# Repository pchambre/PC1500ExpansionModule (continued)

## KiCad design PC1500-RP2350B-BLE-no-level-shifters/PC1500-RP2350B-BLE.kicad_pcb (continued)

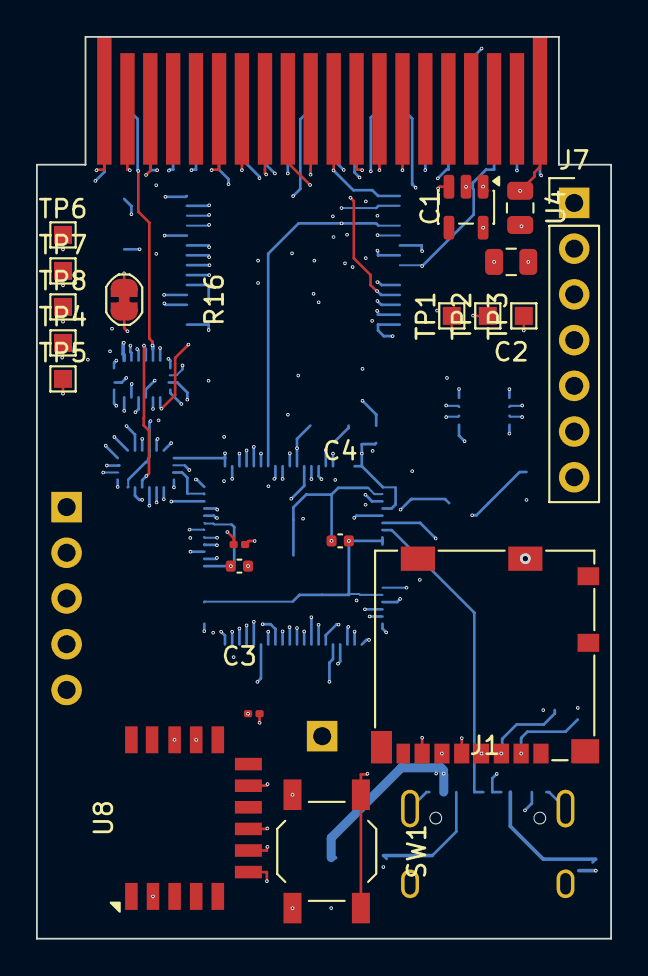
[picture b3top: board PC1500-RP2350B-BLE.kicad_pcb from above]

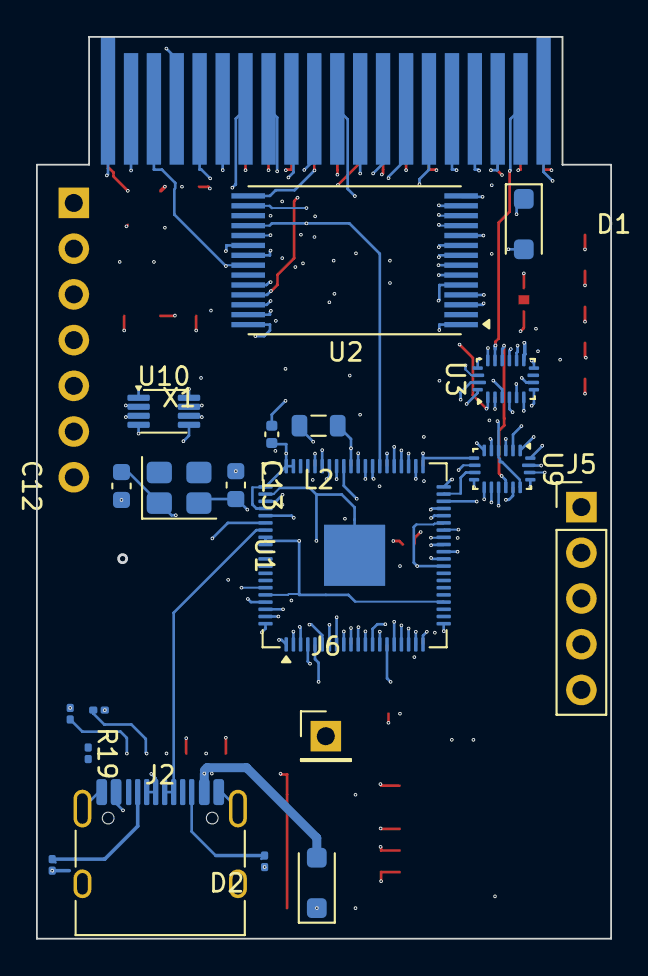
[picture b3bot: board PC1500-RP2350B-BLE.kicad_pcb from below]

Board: 8 copper layers, 31.9 x 50.1 mm, 41 parts (20 on the bottom side), 77 nets.

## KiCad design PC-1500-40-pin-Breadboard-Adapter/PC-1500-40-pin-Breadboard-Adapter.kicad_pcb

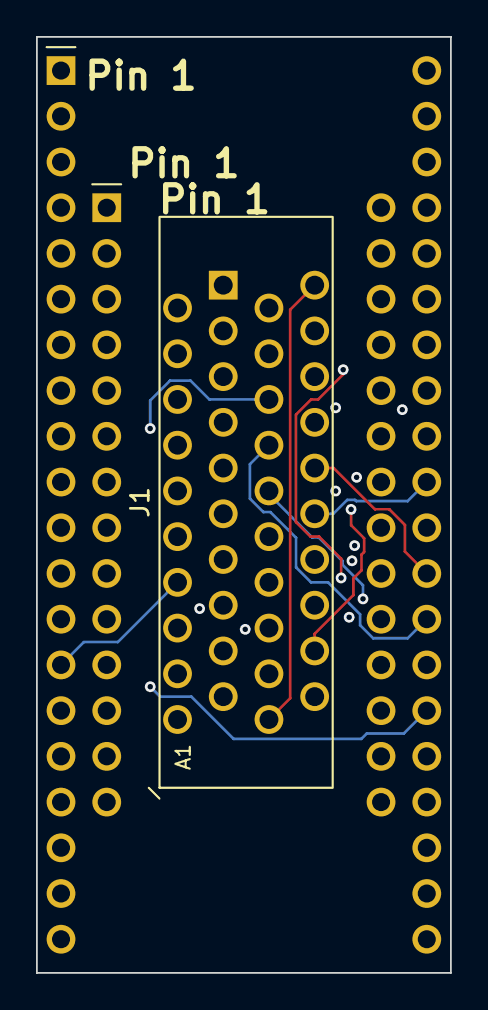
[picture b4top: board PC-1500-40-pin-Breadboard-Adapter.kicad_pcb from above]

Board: 4 copper layers, 23.0 x 52.0 mm, 3 parts (0 on the bottom side), 39 nets.

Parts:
J1: RBB20DHHN; Sullins_RBB20DHHN_2x20_P1.27mm_Staggered
J2: DIP-40 0.8in (breadboard); DIP-40_W20.32mm_Holes
J3: DIP-28 0.6in (EPROM socket); DIP-28_W15.24mm_Holes

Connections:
/AD0: J1.37, J2.37
/AD1: J1.36, J2.36
/AD2: J1.35, J2.35
/AD3: J1.34, J2.34
/AD4: J1.33, J2.33
/AD5: J1.32, J2.32
/AD6: J1.31, J2.31
/AD7: J1.30, J2.30
/AD8: J1.29, J2.29
/AD9: J1.28, J2.28
/AD10: J1.27, J2.27
/AD11: J1.26, J2.26
/AD12: J1.25, J2.25
/AD13: J1.24, J2.24
/AD14: J1.23, J2.23
/AD15: J1.22, J2.22
/CART_PIN5: J1.5, J2.5
/D0: J1.14, J2.14
/D1: J1.13, J2.13
/D2: J1.12, J2.12
/D3: J1.11, J2.11
/D4: J1.10, J2.10
/D5: J1.9, J2.9
/D6: J1.8, J2.8
/D7: J1.7, J2.7
/DME0: J1.6, J2.6
/GND: J1.21, J1.40, J2.21, J2.40
/INHIBIT: J1.15, J2.15
/OD: J1.38, J2.38
/PU: J1.2, J2.2
/PV: J1.3, J2.3
/RW: J1.39, J2.39
/S1: J1.16, J2.16
/S2: J1.17, J2.17
/S3: J1.18, J2.18
/VCC: J1.1, J2.1
/VGG: J1.20, J2.20
/Y0: J1.4, J2.4
/Y2: J1.19, J2.19

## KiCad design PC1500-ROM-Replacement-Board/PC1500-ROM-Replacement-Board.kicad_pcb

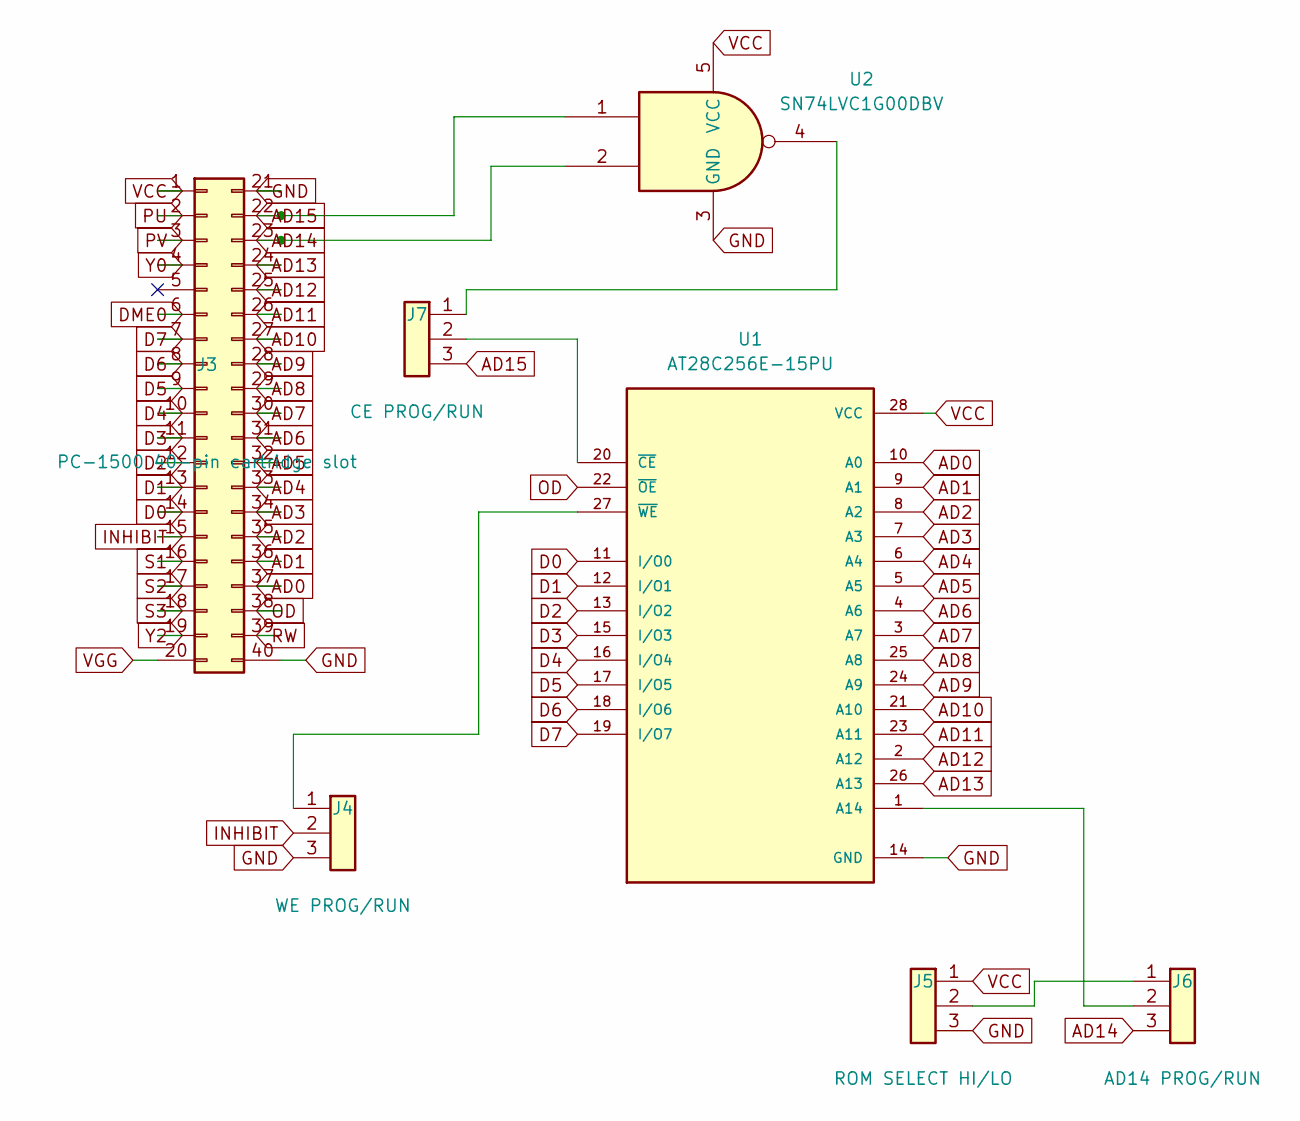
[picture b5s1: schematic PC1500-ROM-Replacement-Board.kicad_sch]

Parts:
J3: PC-1500 40-pin cartridge slot; SHARP-PC-CARTRIDGE
J4: WE PROG/RUN; PinHeader_1x03_P2.54mm_Vertical
J5: ROM SELECT HI/LO; PinHeader_1x03_P2.54mm_Vertical
J6: AD14 PROG/RUN; PinHeader_1x03_P2.54mm_Vertical
J7: CE PROG/RUN; PinHeader_1x03_P2.54mm_Vertical
U1: AT28C256E-15PU; SOIC-28W_7.5x17.9mm_P1.27mm; PARTREV B
U2: SN74LVC1G00DBV; SOT-23-5

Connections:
AD0: J3.37, U1.10 (A0)
AD1: J3.36, U1.9 (A1)
AD2: J3.35, U1.8 (A2)
AD3: J3.34, U1.7 (A3)
AD4: J3.33, U1.6 (A4)
AD5: J3.32, U1.5 (A5)
AD6: J3.31, U1.4 (A6)
AD7: J3.30, U1.3 (A7)
AD8: J3.29, U1.25 (A8)
AD9: J3.28, U1.24 (A9)
AD10: J3.27, U1.21 (A10)
AD11: J3.26, U1.23 (A11)
AD12: J3.25, U1.2 (A12)
AD13: J3.24, U1.26 (A13)
AD14: J3.23, J6.3, U2.2
AD15: J3.22, J7.3, U2.1
D0: J3.14, U1.11 (I/O0)
D1: J3.13, U1.12 (I/O1)
D2: J3.12, U1.13 (I/O2)
D3: J3.11, U1.15 (I/O3)
D4: J3.10, U1.16 (I/O4)
D5: J3.9, U1.17 (I/O5)
D6: J3.8, U1.18 (I/O6)
D7: J3.7, U1.19 (I/O7)
DME0: J3.6
GND: J3.21, J3.40, J4.3, J5.3, U1.14 (GND), U2.3 (GND)
INHIBIT: J3.15, J4.2
unnamed: J4.1, U1.27 (~WE)
unnamed: J5.2, J6.1
unnamed: J6.2, U1.1 (A14)
unnamed: J7.1, U2.4
unnamed: J7.2, U1.20 (~CE)
OD: J3.38, U1.22 (~OE)
PU: J3.2
PV: J3.3
RW: J3.39
S1: J3.16
S2: J3.17
S3: J3.18
VCC: J3.1, J5.1, U1.28 (VCC), U2.5 (VCC)
VGG: J3.20
Y0: J3.4
Y2: J3.19

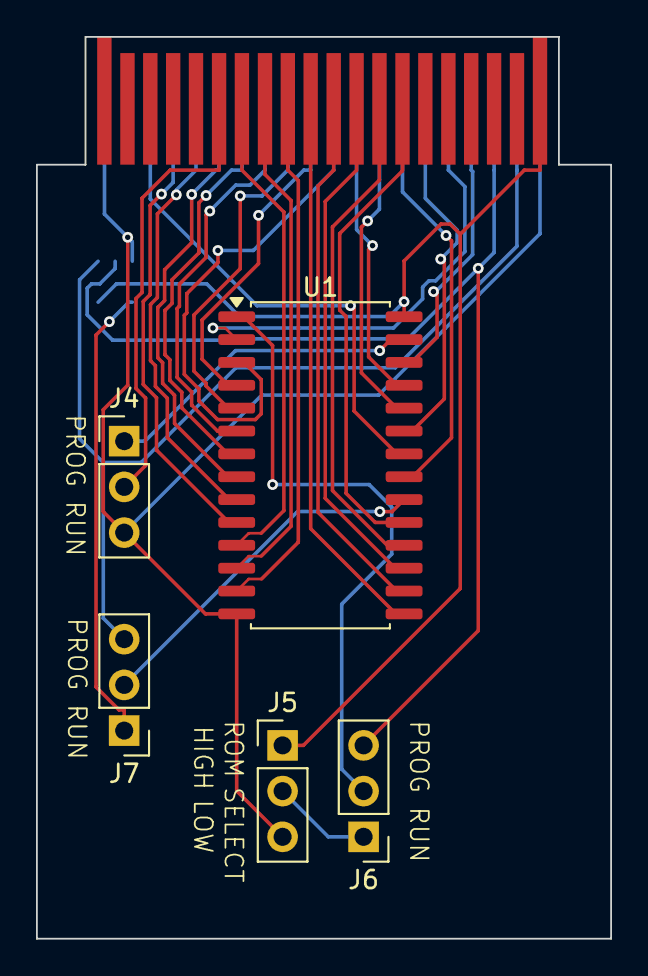
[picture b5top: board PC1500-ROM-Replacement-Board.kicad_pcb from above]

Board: 2 copper layers, 31.9 x 50.1 mm, 7 parts (1 on the bottom side), 33 nets.

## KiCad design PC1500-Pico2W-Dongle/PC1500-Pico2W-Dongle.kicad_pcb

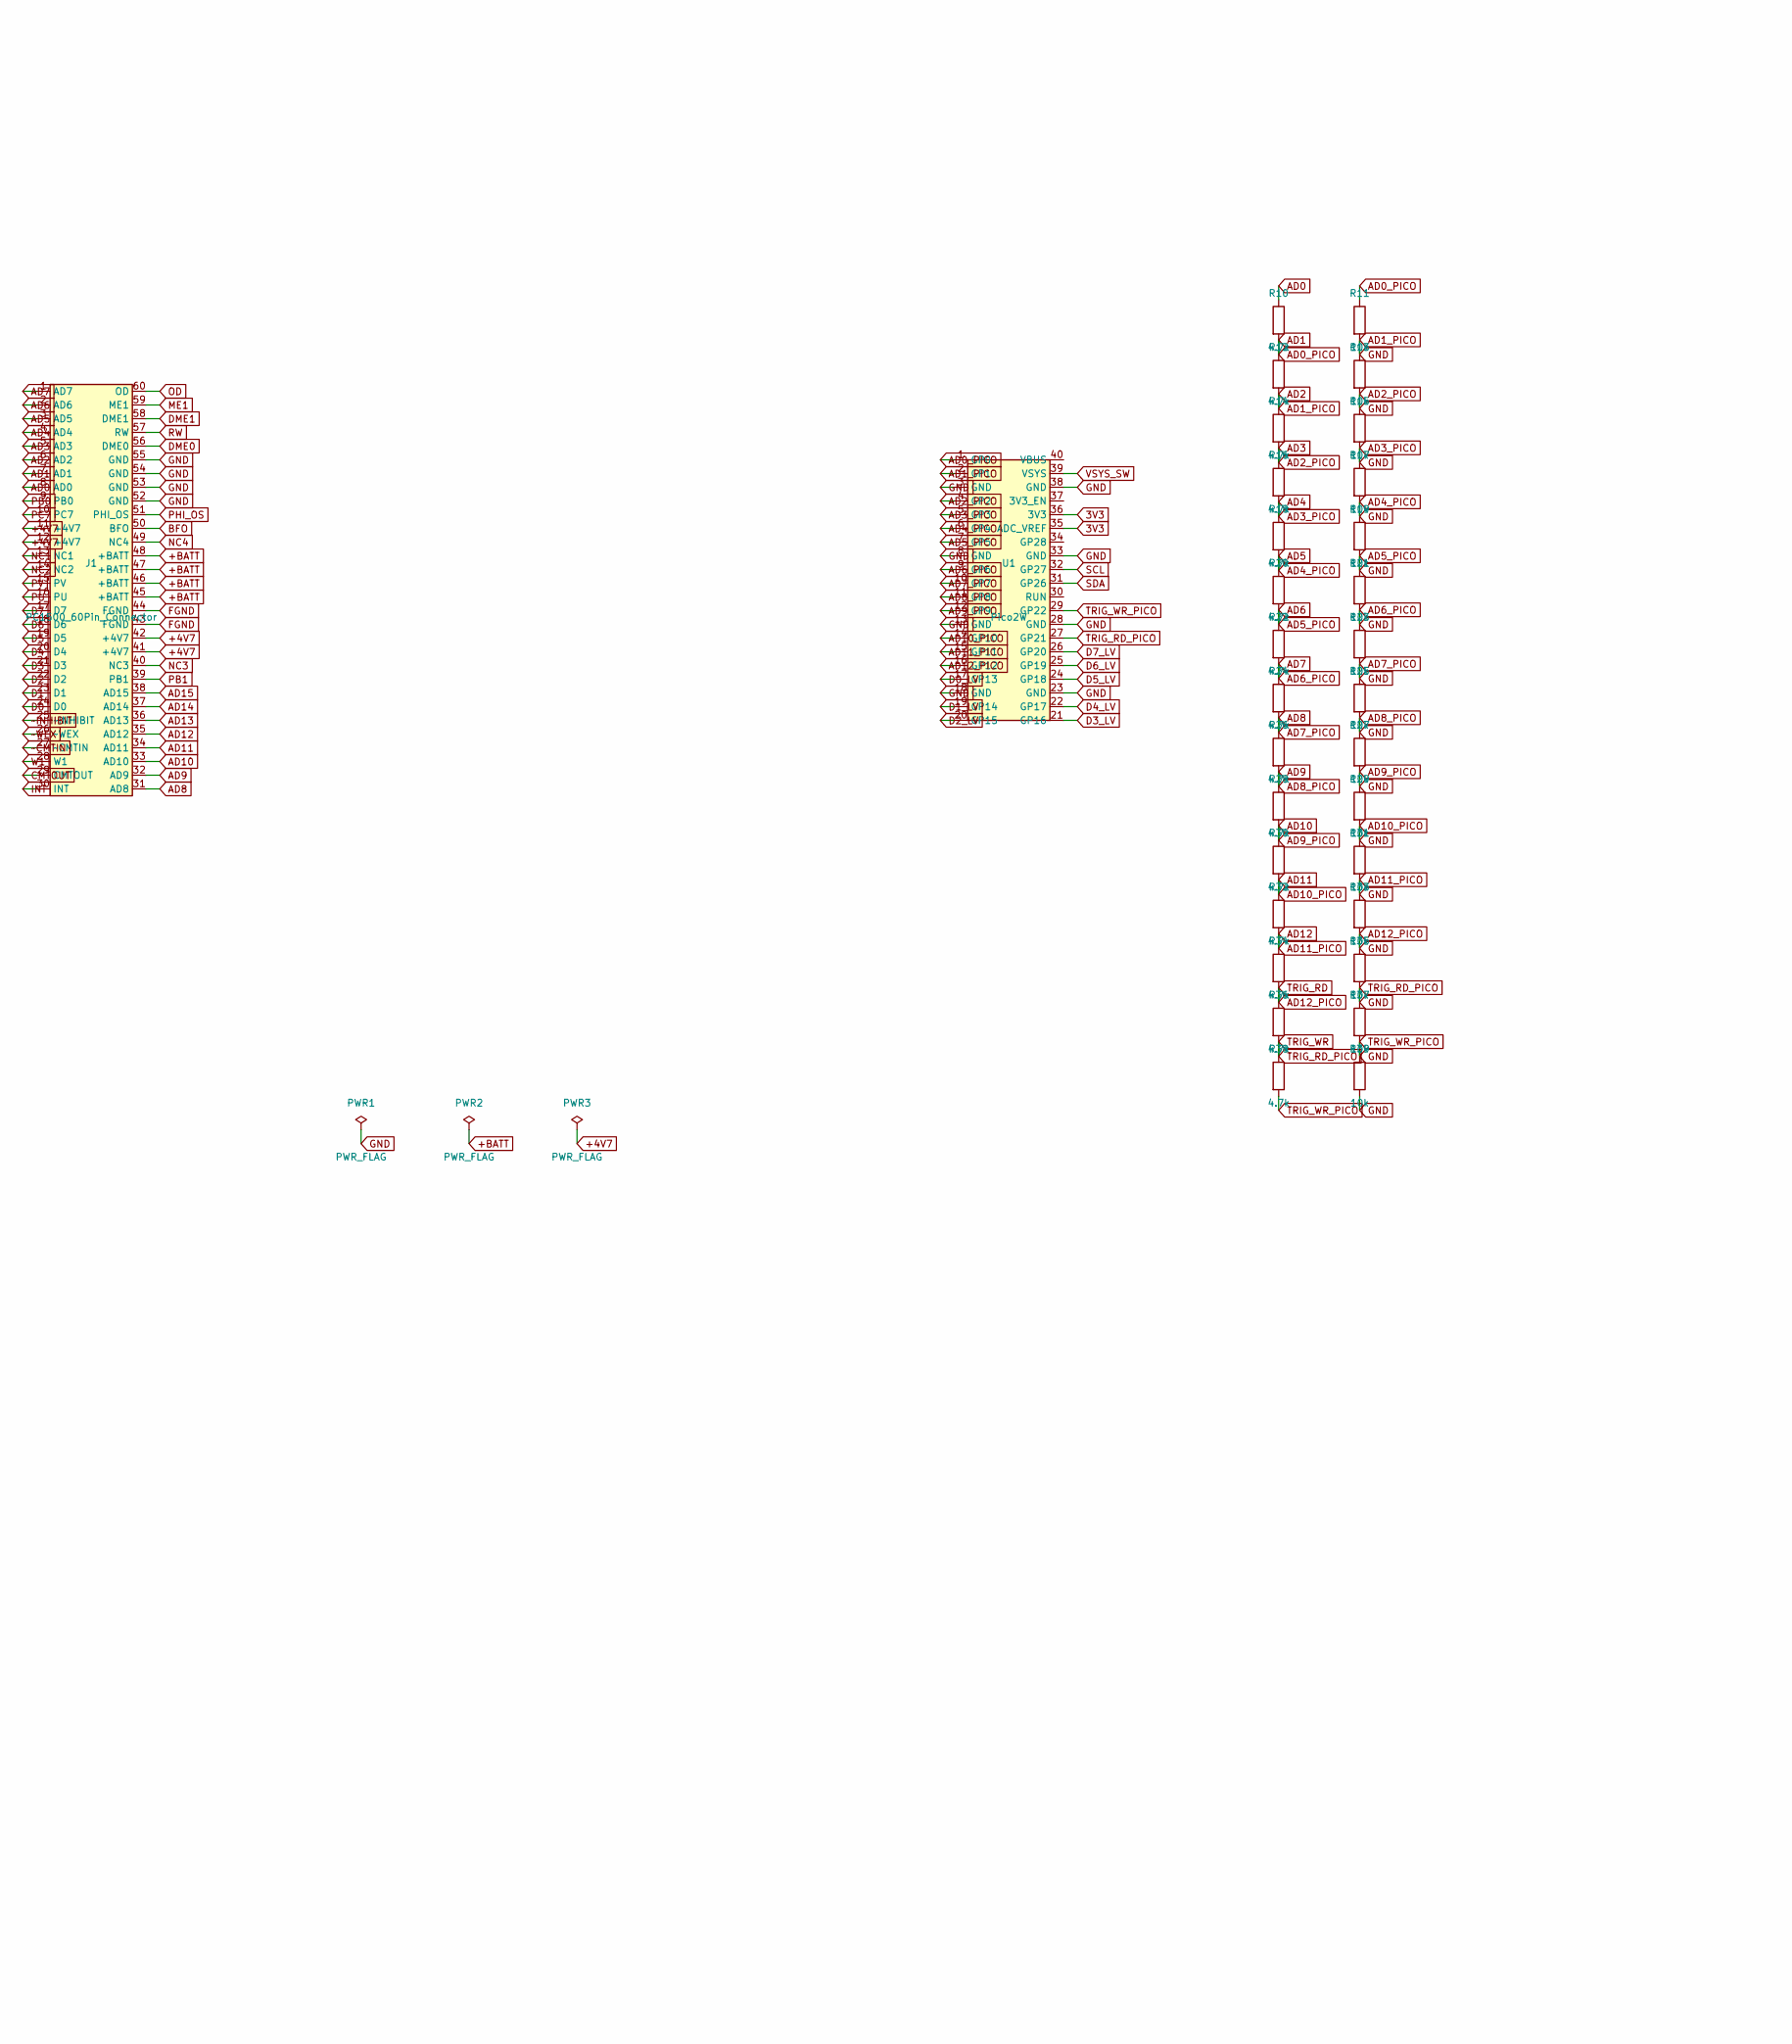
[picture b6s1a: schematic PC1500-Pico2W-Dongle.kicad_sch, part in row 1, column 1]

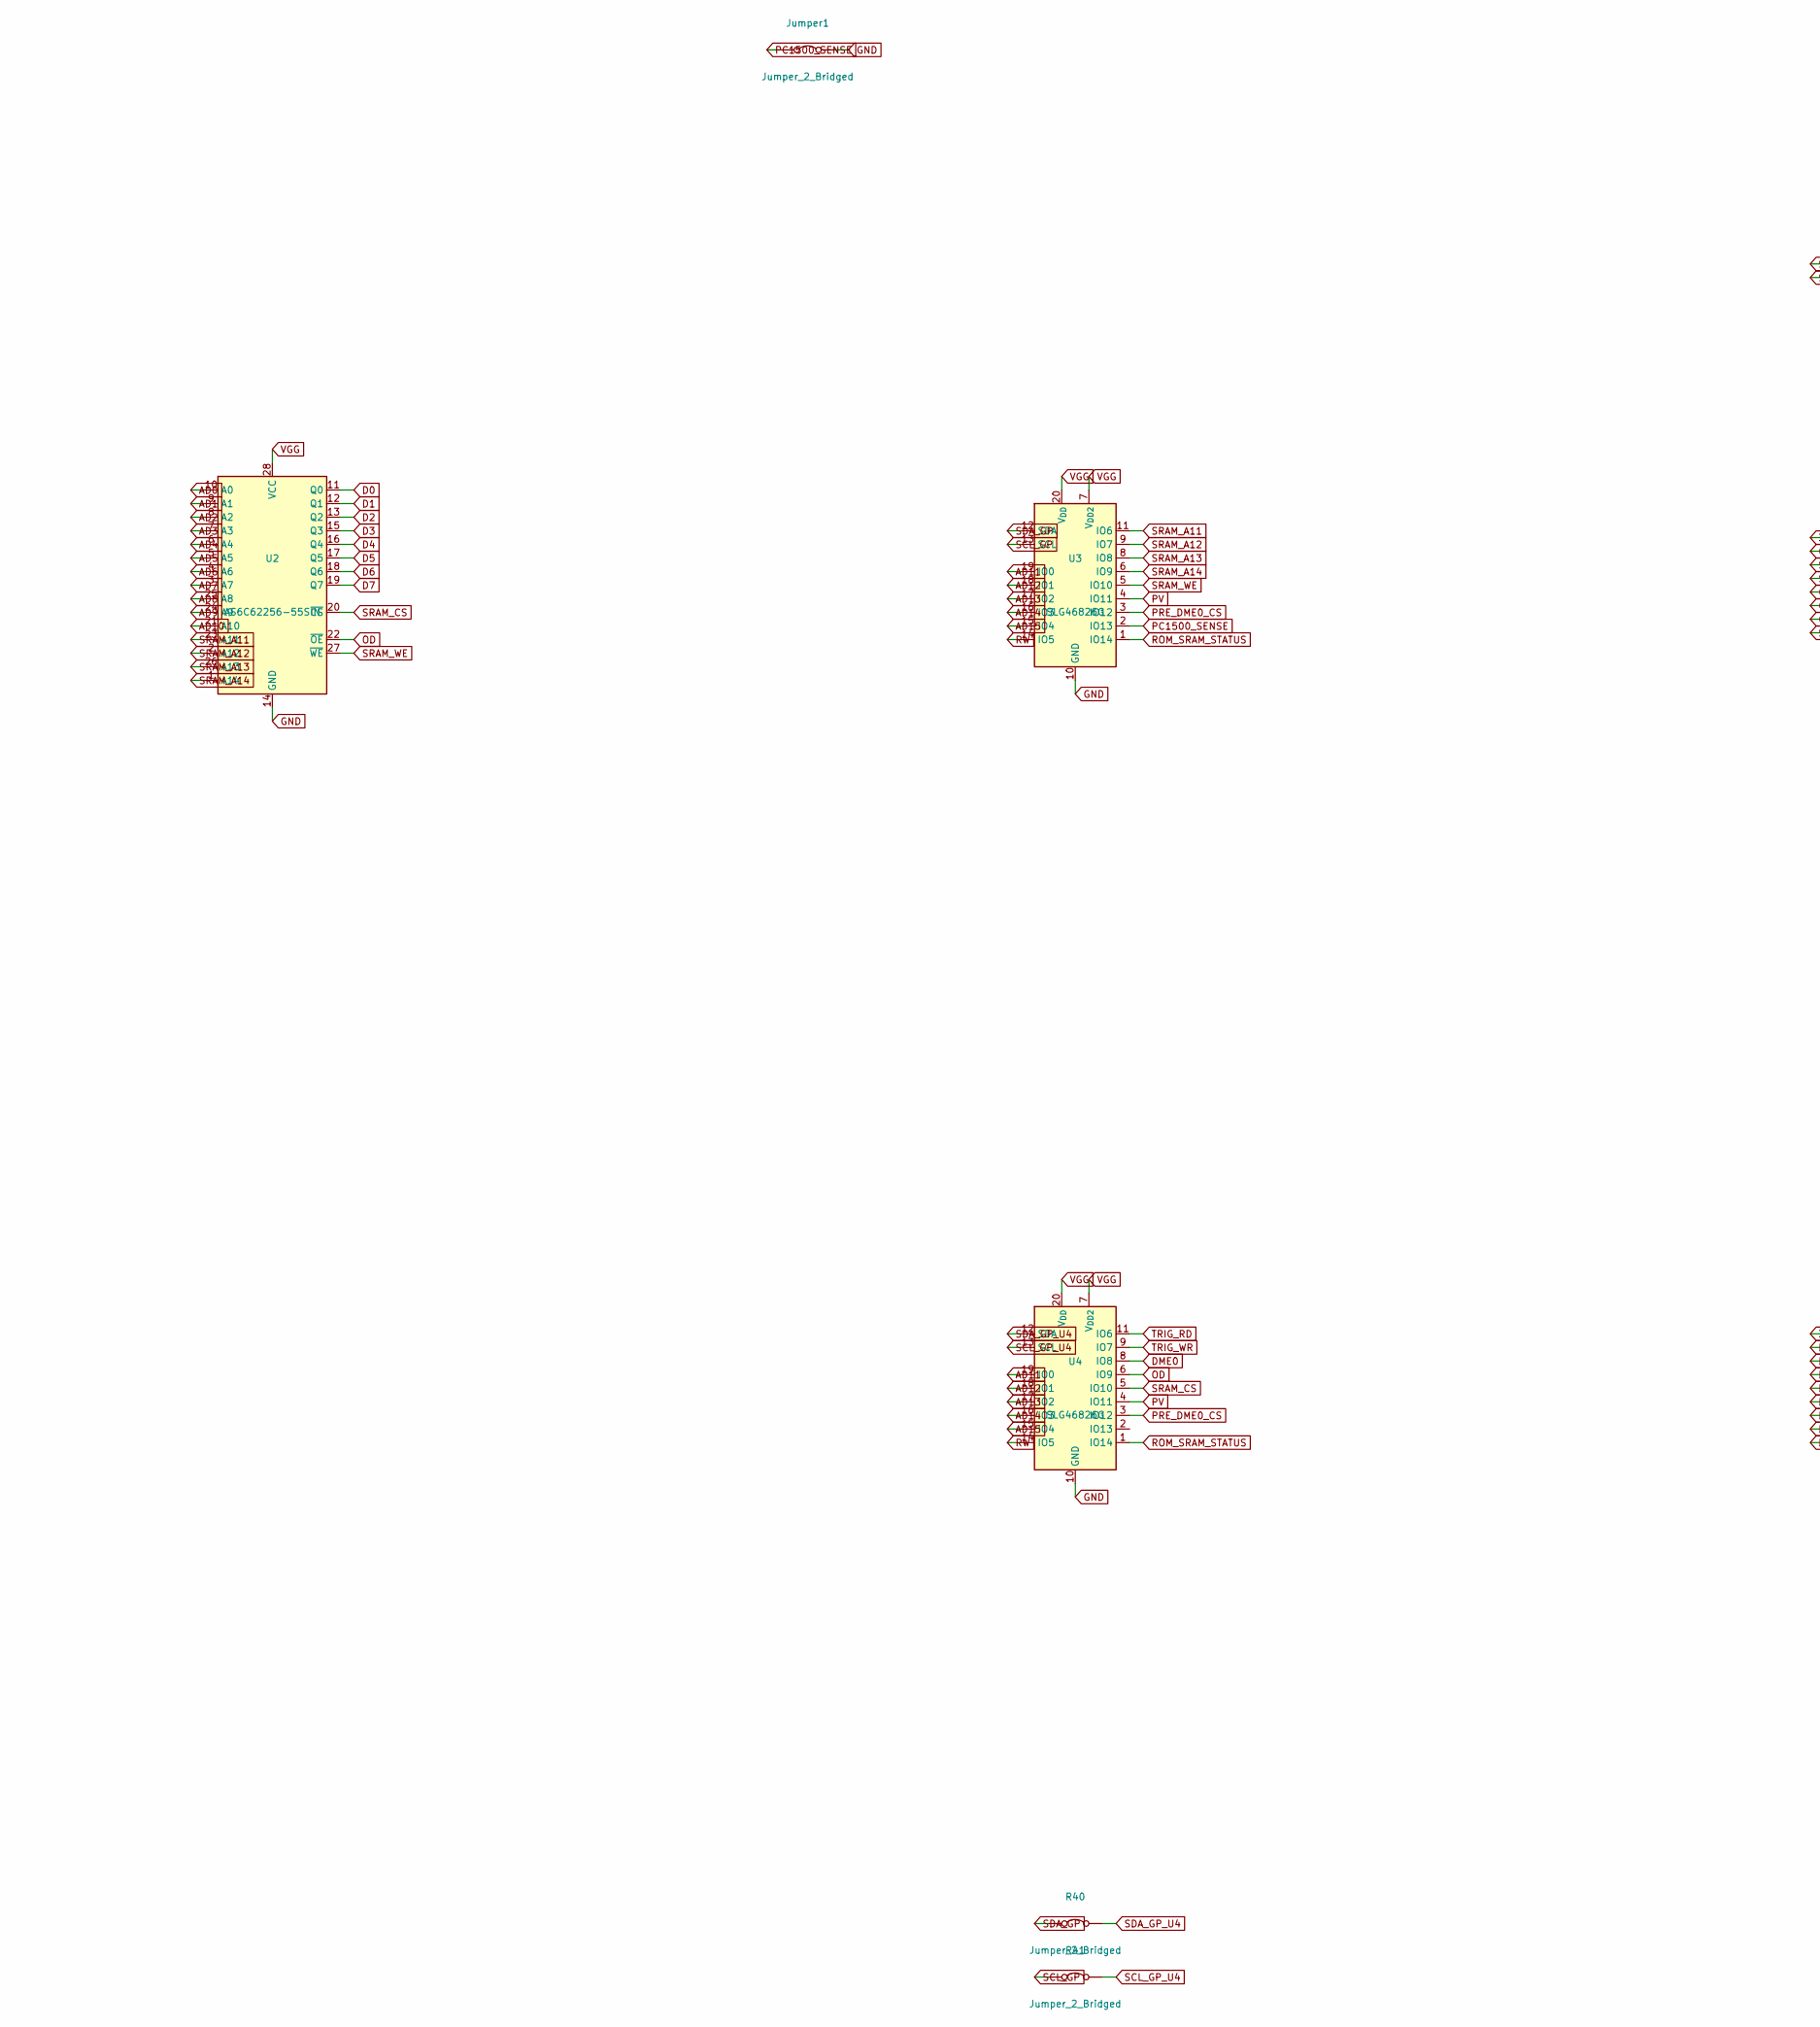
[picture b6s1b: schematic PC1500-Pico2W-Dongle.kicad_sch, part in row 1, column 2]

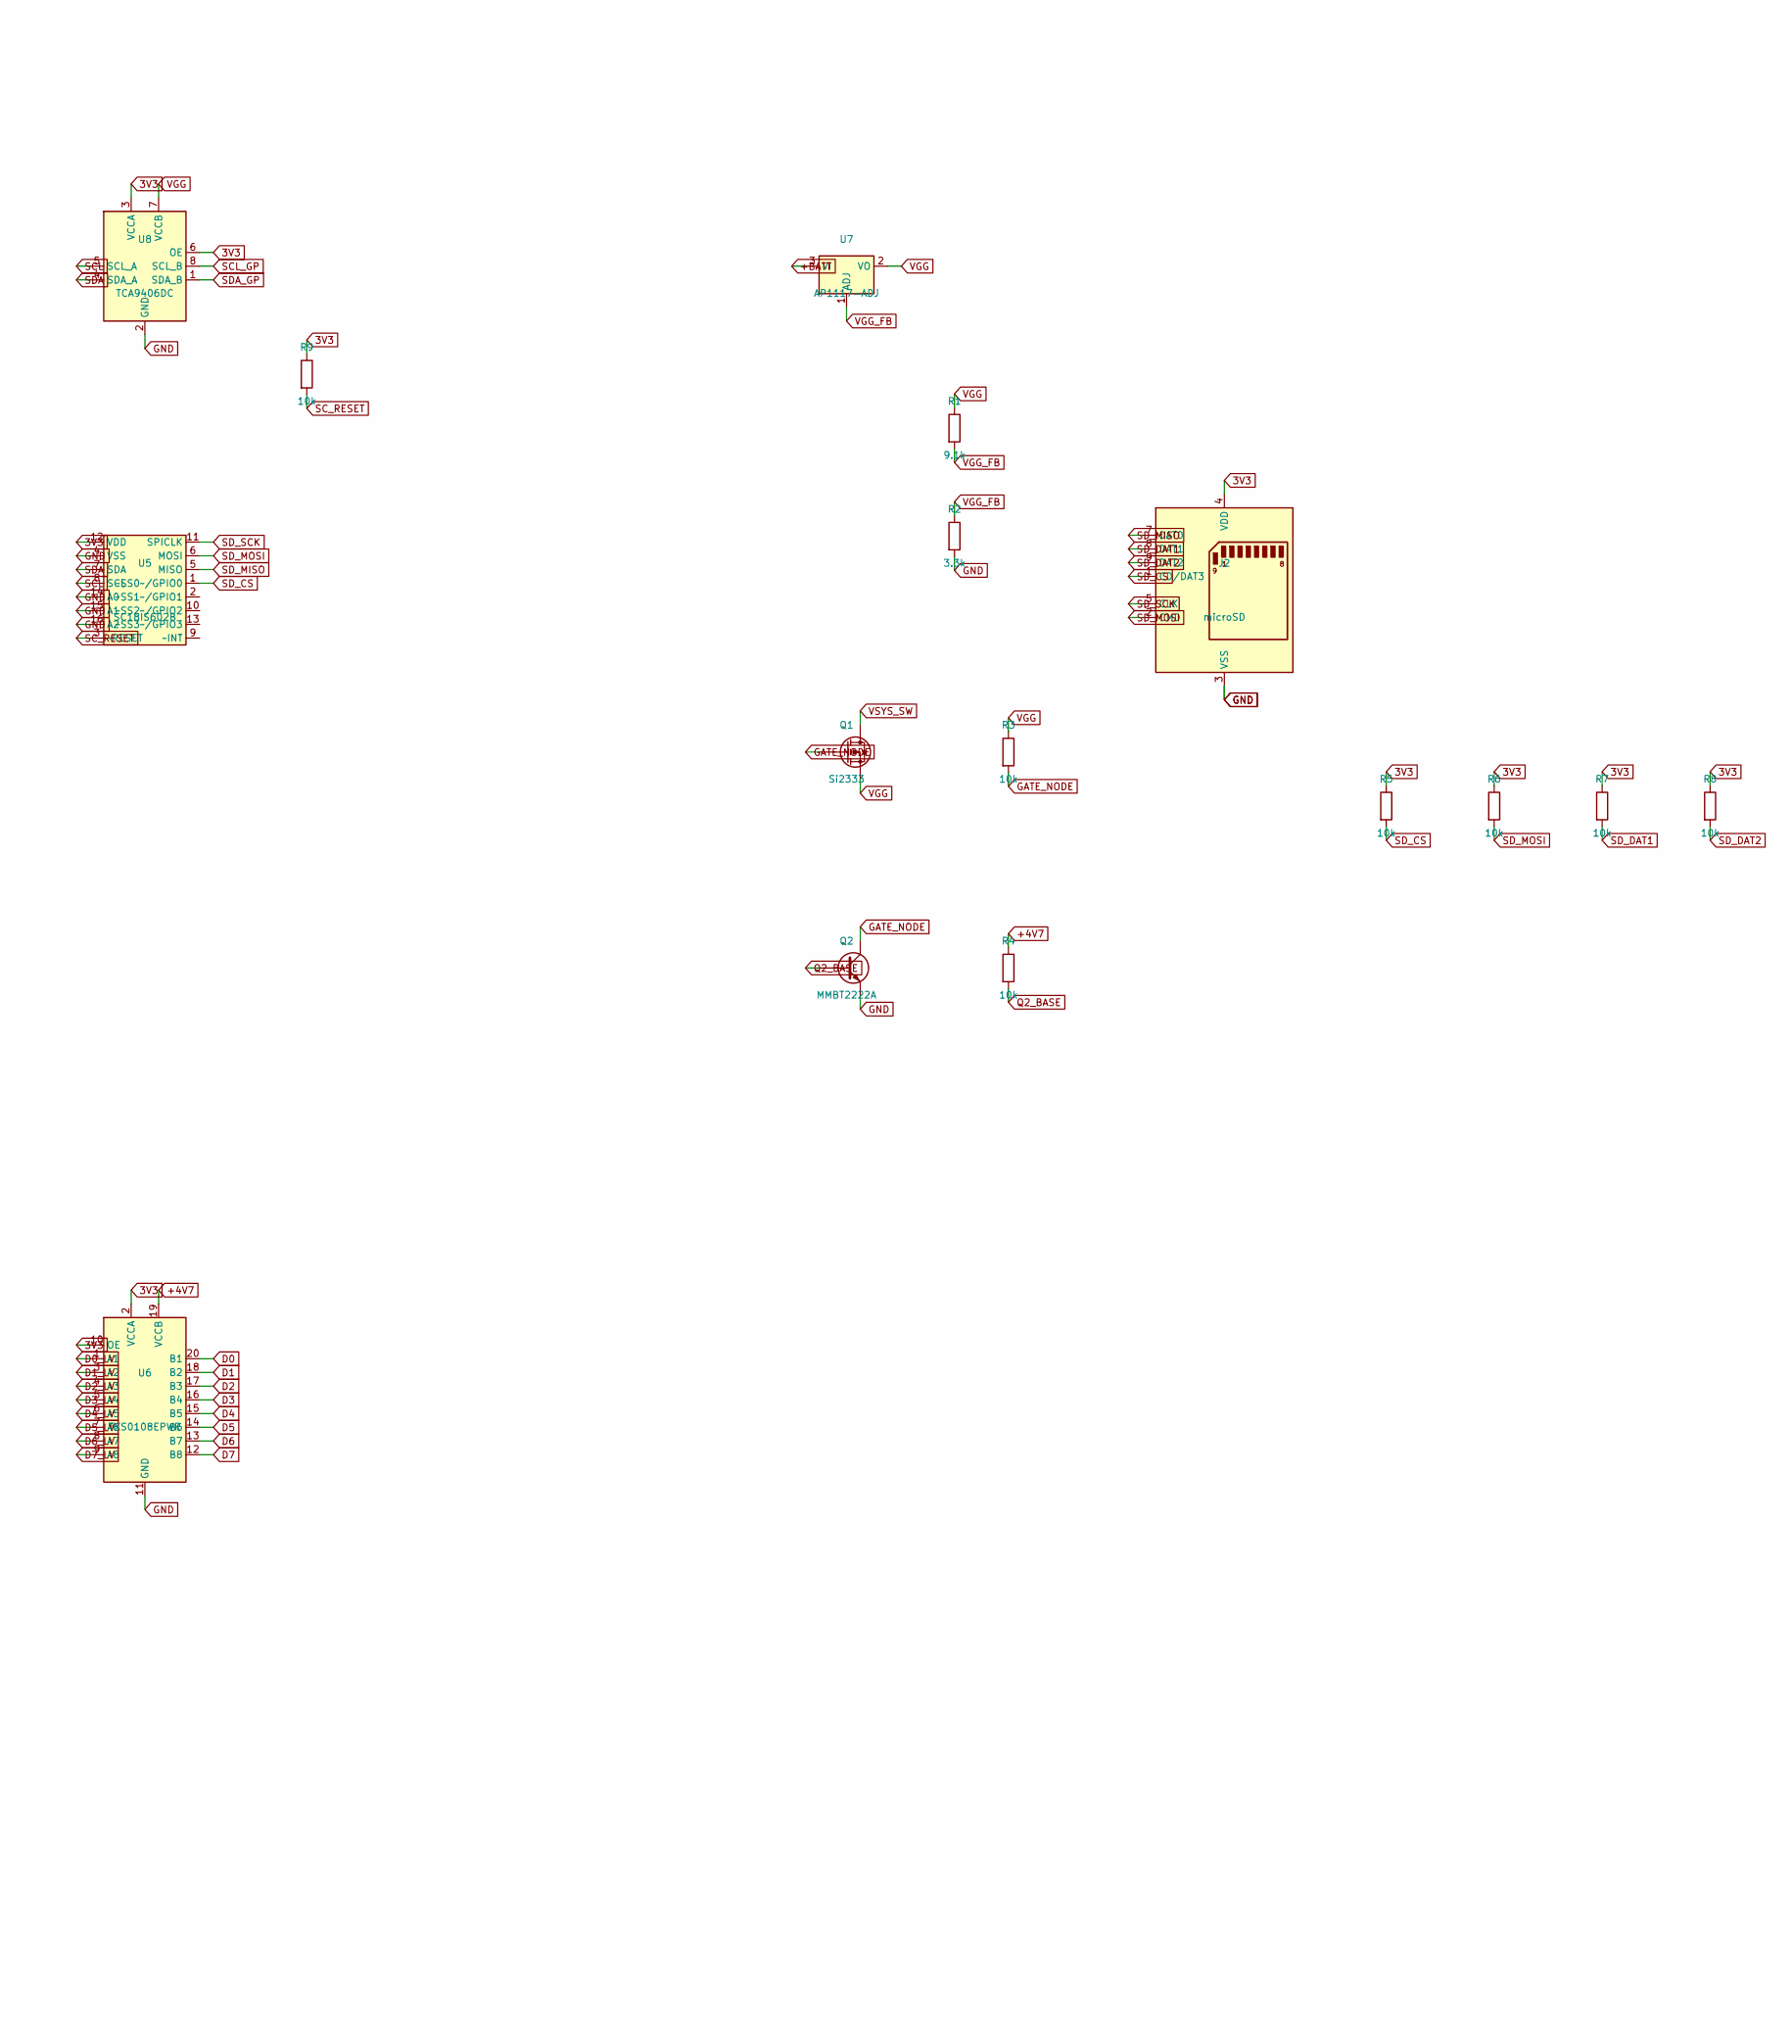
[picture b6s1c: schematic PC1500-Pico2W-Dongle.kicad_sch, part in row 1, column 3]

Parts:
J1: PC1500_60Pin_Connector; HIF6A-60PA-1.27DS
J2: microSD; microSD_HC_Molex_104031-0811
Jumper1: Jumper_2_Bridged; SolderJumper-2_P1.3mm_Bridged_RoundedPad1.0x1.5mm
PWR1, PWR2, PWR3: PWR_FLAG
Q1: Si2333; SOT-23
Q2: MMBT2222A; SOT-23
R1: 9.1k; R_0201_0603Metric
R2: 3.3k; R_0201_0603Metric
R3, R4, R5, R6, R7, R8, R9, R11, R13, R15, R17, R19, R21, R23, R25, R27, R29, R31, R33, R35, R37, R39: 10k; R_0201_0603Metric
R10, R12, R14, R16, R18, R20, R22, R24, R26, R28, R30, R32, R34, R36, R38: 4.7k; R_0201_0603Metric
R40, R41: Jumper_2_Bridged; SolderJumper-2_P1.3mm_Bridged_RoundedPad1.0x1.5mm
U1: Pico2W; Pico2W-Socket
U2: AS6C62256-55SIN; SOP-28_8.4x18.16mm_P1.27mm
U3, U4: SLG46826G; TSSOP-20_4.4x6.5mm_P0.65mm
U5: SC18IS602B; TSSOP-16_4.4x5mm_P0.65mm
U6: TXS0108EPWR; TSSOP-20_4.4x6.5mm_P0.65mm
U7: AP1117-ADJ; SOT-223-3_TabPin2
U8: TCA9406DC; VSSOP-8_3x3mm_P0.65mm

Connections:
3V3: J2.4 (VDD), R5.1, R6.1, R7.1, R8.1, R9.1, U1.35 (ADC_VREF), U1.36 (3V3), U5.12 (VDD), U6.2 (VCCA), U6.10 (OE), U8.3 (VCCA), U8.6 (OE)
+4V7: J1.11 (+4V7), J1.12 (+4V7), J1.41 (+4V7), J1.42 (+4V7), PWR3.1, R4.1, U6.19 (VCCB)
+BATT: J1.45 (+BATT), J1.46 (+BATT), J1.47 (+BATT), J1.48 (+BATT), PWR2.1, U7.3 (VI)
AD0: J1.8 (AD0), R10.1, U2.10 (A0)
AD0_PICO: R10.2, R11.1, U1.1 (GP0)
AD1: J1.7 (AD1), R12.1, U2.9 (A1)
AD1_PICO: R12.2, R13.1, U1.2 (GP1)
AD2: J1.6 (AD2), R14.1, U2.8 (A2)
AD2_PICO: R14.2, R15.1, U1.4 (GP2)
AD3: J1.5 (AD3), R16.1, U2.7 (A3)
AD3_PICO: R16.2, R17.1, U1.5 (GP3)
AD4: J1.4 (AD4), R18.1, U2.6 (A4)
AD4_PICO: R18.2, R19.1, U1.6 (GP4)
AD5: J1.3 (AD5), R20.1, U2.5 (A5)
AD5_PICO: R20.2, R21.1, U1.7 (GP5)
AD6: J1.2 (AD6), R22.1, U2.4 (A6)
AD6_PICO: R22.2, R23.1, U1.9 (GP6)
AD7: J1.1 (AD7), R24.1, U2.3 (A7)
AD7_PICO: R24.2, R25.1, U1.10 (GP7)
AD8: J1.31 (AD8), R26.1, U2.25 (A8)
AD8_PICO: R26.2, R27.1, U1.11 (GP8)
AD9: J1.32 (AD9), R28.1, U2.24 (A9)
AD9_PICO: R28.2, R29.1, U1.12 (GP9)
AD10: J1.33 (AD10), R30.1, U2.21 (A10)
AD10_PICO: R30.2, R31.1, U1.14 (GP10)
AD11: J1.34 (AD11), R32.1, U3.19 (IO0), U4.19 (IO0)
AD11_PICO: R32.2, R33.1, U1.15 (GP11)
AD12: J1.35 (AD12), R34.1, U3.18 (IO1), U4.18 (IO1)
AD12_PICO: R34.2, R35.1, U1.16 (GP12)
AD13: J1.36 (AD13), U3.17 (IO2), U4.17 (IO2)
AD14: J1.37 (AD14), U3.16 (IO3), U4.16 (IO3)
AD15: J1.38 (AD15), U3.15 (IO4), U4.15 (IO4)
BFO: J1.50 (BFO)
CMTOUT: J1.29 (CMTOUT)
D0: J1.24 (D0), U2.11 (Q0), U6.20 (B1)
D0_LV: U1.17 (GP13), U6.1 (A1)
D1: J1.23 (D1), U2.12 (Q1), U6.18 (B2)
D1_LV: U1.19 (GP14), U6.3 (A2)
D2: J1.22 (D2), U2.13 (Q2), U6.17 (B3)
D2_LV: U1.20 (GP15), U6.4 (A3)
D3: J1.21 (D3), U2.15 (Q3), U6.16 (B4)
D3_LV: U1.21 (GP16), U6.5 (A4)
D4: J1.20 (D4), U2.16 (Q4), U6.15 (B5)
D4_LV: U1.22 (GP17), U6.6 (A5)
D5: J1.19 (D5), U2.17 (Q5), U6.14 (B6)
D5_LV: U1.24 (GP18), U6.7 (A6)
D6: J1.18 (D6), U2.18 (Q6), U6.13 (B7)
D6_LV: U1.25 (GP19), U6.8 (A7)
D7: J1.17 (D7), U2.19 (Q7), U6.12 (B8)
D7_LV: U1.26 (GP20), U6.9 (A8)
DME0: J1.56 (DME0), U4.8 (IO8)
DME1: J1.58 (DME1)
FGND: J1.43 (FGND), J1.44 (FGND)
GATE_NODE: Q1.1, Q1.G, Q2.3, Q2.C, R3.2
GND: J1.52 (GND), J1.53 (GND), J1.54 (GND), J1.55 (GND), J2.3 (VSS), J2.6 (VSS), Jumper1.2 (B), PWR1.1, Q2.2, Q2.E, R2.2, R11.2, R13.2, R15.2, R17.2, R19.2, R21.2, R23.2, R25.2, R27.2, R29.2, R31.2, R33.2, R35.2, R37.2, R39.2, U1.3 (GND), U1.8 (GND), U1.13 (GND), U1.18 (GND), U1.23 (GND), U1.28 (GND), U1.33 (GND), U1.38 (GND), U2.14 (GND), U3.10 (GND), U4.10 (GND), U5.4 (VSS), U5.14 (A0), U5.15 (A1), U5.16 (A2), U6.11 (GND), U8.2 (GND)
INT: J1.30 (INT)
ME1: J1.59 (ME1)
NC1: J1.13 (NC1)
NC2: J1.14 (NC2)
NC3: J1.40 (NC3)
NC4: J1.49 (NC4)
OD: J1.60 (OD), U2.22 (~OE), U4.6 (IO9)
PB0: J1.9 (PB0)
PB1: J1.39 (PB1)
PC7: J1.10 (PC7)
PC1500_SENSE: Jumper1.1 (A), U3.2 (IO13)
PHI_OS: J1.51 (PHI_OS)
PRE_DME0_CS: U3.3 (IO12), U4.3 (IO12)
PU: J1.16 (PU)
PV: J1.15 (PV), U3.4 (IO11), U4.4 (IO11)
Q2_BASE: Q2.1, Q2.B, R4.2
ROM_SRAM_STATUS: U3.1 (IO14), U4.1 (IO14)
RW: J1.57 (RW), U3.14 (IO5), U4.14 (IO5)
SCL: U1.32 (GP27), U5.8 (SCL), U8.5 (SCL_A)
SCL_GP: R41.1 (A), U3.13 (SCL), U8.8 (SCL_B)
SCL_GP_U4: R41.2 (B), U4.13 (SCL)
SC_RESET: R9.2, U5.3 (~RESET)
SDA: U1.31 (GP26), U5.7 (SDA), U8.4 (SDA_A)
SDA_GP: R40.1 (A), U3.12 (SDA), U8.1 (SDA_B)
SDA_GP_U4: R40.2 (B), U4.12 (SDA)
SD_CS: J2.1 (CD/DAT3), R5.2, U5.1 (~SS0~/GPIO0)
SD_DAT1: J2.8 (DAT1), R7.2
SD_DAT2: J2.9 (DAT2), R8.2
SD_MISO: J2.7 (DAT0), U5.5 (MISO)
SD_MOSI: J2.2 (CMD), R6.2, U5.6 (MOSI)
SD_SCK: J2.5 (CLK), U5.11 (SPICLK)
SRAM_A11: U2.23 (A11), U3.11 (IO6)
SRAM_A12: U2.2 (A12), U3.9 (IO7)
SRAM_A13: U2.26 (A13), U3.8 (IO8)
SRAM_A14: U2.1 (A14), U3.6 (IO9)
SRAM_CS: U2.20 (~CS), U4.5 (IO10)
SRAM_WE: U2.27 (~WE), U3.5 (IO10)
TRIG_RD: R36.1, U4.11 (IO6)
TRIG_RD_PICO: R36.2, R37.1, U1.27 (GP21)
TRIG_WR: R38.1, U4.9 (IO7)
TRIG_WR_PICO: R38.2, R39.1, U1.29 (GP22)
VGG: Q1.2, Q1.S, R1.1, R3.1, U2.28 (VCC), U3.7 (V_{DD2}), U3.20 (V_{DD}), U4.7 (V_{DD2}), U4.20 (V_{DD}), U7.2 (VO), U8.7 (VCCB)
VGG_FB: R1.2, R2.1, U7.1 (ADJ)
VSYS_SW: Q1.3, Q1.D, U1.39 (VSYS)
W1: J1.28 (W1)
~CMTIN: J1.27 (~CMTIN)
~INHIBIT: J1.25 (~INHIBIT)
~WEX: J1.26 (~WEX)

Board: 2 copper layers, 54 parts (0 on the bottom side), 85 nets, no tracks yet.
